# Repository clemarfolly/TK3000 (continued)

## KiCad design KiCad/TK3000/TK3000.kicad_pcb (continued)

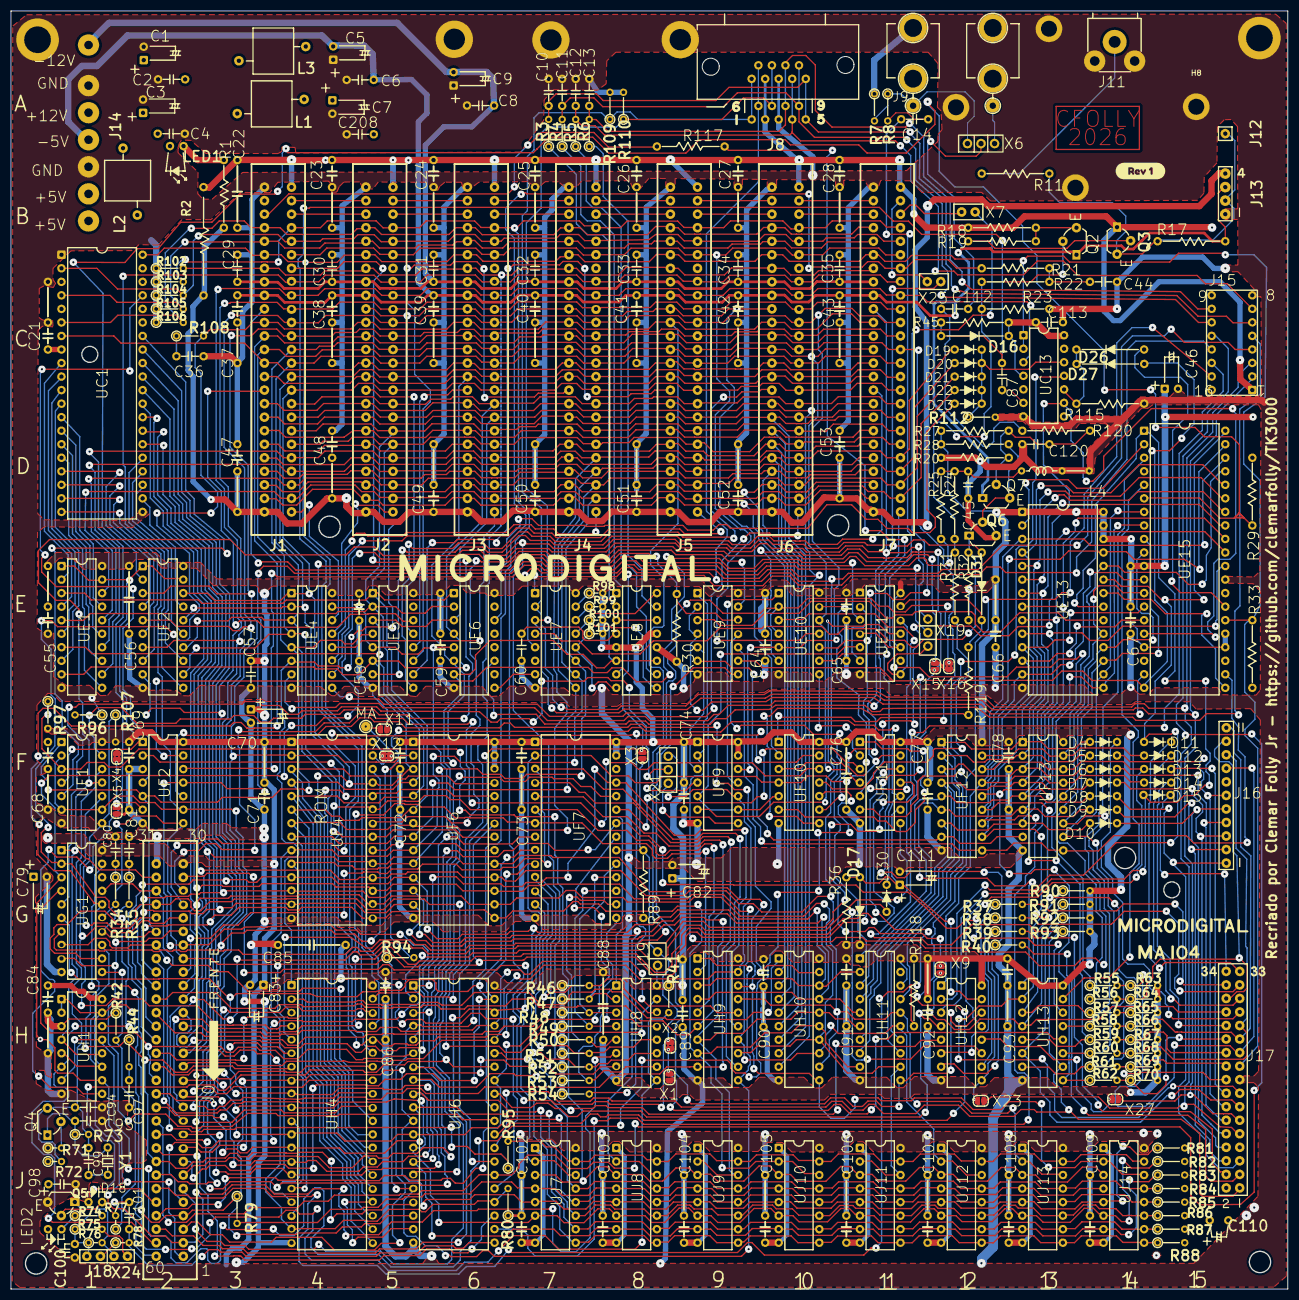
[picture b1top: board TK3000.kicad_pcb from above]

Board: 2 copper layers, 239.6 x 239.9 mm, 329 parts (0 on the bottom side), 320 nets.

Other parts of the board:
kibuzzard-6AD58770: G***; kibuzzard-6AD58770

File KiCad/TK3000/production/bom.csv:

Designator,Footprint,Quantity,Value,LCSC Part #
"C1, C111, C3, C5, C79, C82, C9",C_Elet_111,7,10uF,
"C10, C11, C12, C13",C_Disc_5.08,4,22nF,
C100,C_Disc_C100,1,100nF,
"C101, C112, C113, C2, C208, C29, C30, C31, C32, C33, C34, C35, C4, C57, C6, C8",C_Disc_5.08,16,100nF,
"C102, C103, C104, C105, C106, C107, C108, C109, C21, C23, C24, C25, C26, C27, C28, C37, C38, C39, C40, C41, C42, C43, C47, C48, C49, C50, C51, C52, C53, C55, C58, C59, C64, C66, C67, C68, C69, C71, C72, C73, C74, C77, C78, C84, C86, C89, C90, C91, C92, C93",C_Disc_5.08_12.7mm,50,100nF,
C110,C_Elet_C110,1,10uF,
"C120, C87",C_Disc_5.08,2,C,
C14,C_Disc_5.08,1,47nF,
"C22, C56, C76, C85, C88",C_Disc_12.7mm,5,100nF,
"C36, C80, C81, C97",C_Disc_5.08,4,220pF,
"C44, C94, C95",C_Disc_5.08,3,100pF,
C45,C_Disc_5.08,1,47pF,
"C46, C7, C70, C83",C_Elet_Tipo2,4,10uF,
C60,C_Disc_5.08,1,100n,
C65,C65_Disc_5.08_12.7mm,1,100nF,
C98,CP_Disc_5.08,1,10uF,
C99,C_Disc_5.08,1,33pF,
"D10, D11, D12, D13, D14, D15, D19, D20, D21, D22, D23, D30, D4, D5, D6, D7, D8, D9",D_5.08,18,1N914,
"D16, D17, D26, D27, D31",D_12.7,5,1N914,
D18,D_D18,1,1N914,
J0,SLOT-60_W5.08,1,~,
"J1, J2, J3, J4, J5, J6, J7",SLOT-50_W5.08,7,~,
J10,EarJack,1,EAR,
J11,"RCA_AV-8,4-5A",1,~,
J12,J12,1,Conn_01x01_Pin,
J13,J13,1,J13,
J14,J14,1,Power Connector,
J15,GAME_IO,1,~,
J16,J16,1,J16,
J17,J17,1,J17,
J18,J18,1,Alto-Falante,
J19,PinHeader_1x02_P2.54mm_Vertical,1,Conn_01x02_Pin,
J8,DB9,1,DE9_Socket,
J9,EarJack,1,EAR/MIC,
"L1, L2, L3",Ind,3,Ind,
L4,Ind_762,1,47uH,
LED1,led1,1,LED,
LED2,led2,1,LED,
"Q2, Q7",BC558,2,BC558,
"Q3, Q5, Q6",BC548,3,BC548,
Q4,BF494,1,BF494,
"R1, R17, R21",Resistor_P12.70mm_Horizontal,3,220R,
"R100, R101, R98, R99",Resistor_P2.54mm_Vertical,4,1k,
"R102, R46, R47, R48, R49, R50, R51, R52, R53, R54, R63, R64, R65, R66, R67, R68, R69, R70",Resistor_P5.08mm_Vertical,18,2k2,
"R103, R104, R105, R106, R107, R109, R110, R112, R41, R42, R55, R56, R57, R58, R59, R60, R61, R62, R90, R91, R92, R93, R94, R96, R97",Resistor_P5.08mm_Vertical,25,1k,
"R108, R34, R35, R44",Resistor_P5.08mm_Vertical,4,120R,
R11,Resistor_P12.70mm_Horizontal,1,100R,
"R115, R117, R118, R120, R18, R25, R29, R30, R31, R32, R89",Resistor_P12.70mm_Horizontal,11,1k,
R119,Resistor_P12.70mm_Horizontal,1,470R,
R19,Resistor_P12.70mm_Horizontal,1,47R,
R2,Res_20.32,1,100R/1W,
"R20, R33",Resistor_P12.70mm_Horizontal,2,4k7,
R22,Resistor_P12.70mm_Horizontal,1,5k6,
"R23, R24",Resistor_P12.70mm_Horizontal,2,6k8,
R27,Resistor_P12.70mm_Horizontal,1,220k,
R28,Resistor_P12.70mm_Horizontal,1,10k,
"R3, R4, R5, R6, R7, R74",Resistor_P5.08mm_Vertical,6,100R,
"R36, R45",Resistor_P12.70mm_Horizontal,2,2k2,
"R37, R38, R39, R40",Resistor_P5.08mm_Vertical,4,220,
R71,Resistor_P2.54mm_Vertical,1,47R,
R72,Resistor_P2.54mm_Vertical,1,470R,
R73,Resistor_P2.54mm_Vertical,1,22k,
R75,Resistor_P5.08mm_Vertical,1,33R,
R76,Resistor_P2.54mm_Vertical,1,75R,
R77,Resistor_P2.54mm_Vertical,1,51k,
R78,Resistor_P2.54mm_Vertical,1,3k3,
"R79, R95",Resistor_P5.08mm_Vertical,2,47R,
R8,Resistor_P5.08mm_Vertical,1,12k,
"R80, R81, R82, R83, R84, R85, R86, R87, R88",Resistor_P5.08mm_Vertical,9,22k,
UC1,DIP-40_W15.24mm,1,6502,
UC13,DIP-14_W7.62mm,1,74LS74,
"UE1, UE2",DIP-20_W7.62mm,2,74LS244,
UE10,UE10_DIP-14_W7.62mm,1,74LS32,
UE11,UE11_DIP-14_W7.62mm,1,74LS74,
UE13,DIP-28_W15.24mm,1,27C128,
UE15,DIP-40_W15.24mm,1,Z80A,
UE4,UE4_DIP-16_W7.62mm,1,74LS138,
"UE5, UE6",DIP-16_W7.62mm,2,74LS138,
UE7,DIP-16_W7.62mm,1,74LS251,
UE8,DIP-16_W7.62mm,1,NE558,
UE9,UE9_DIP-14_W7.62mm,1,74LS32,
UF1,DIP-14_W7.62mm,1,74LS125,
UF10,DIP-14_W7.62mm,1,74LS00,
UF11,DIP-14_W7.62mm,1,74LS08,
UF12,RAM_F12-13,1,2 x 2114,
UF2,DIP-14_W7.62mm,1,74S02,
UF4,ROM_F4-F6,1,27128,
UF7,UF7_DIP-28_W15.24mm,1,27C64,
UF9,DIP-14_W7.62mm,1,74LS86,
UG1,UG1_DIP-20_W7.62mm,1,PAL16R8,
UH1,DIP-16_W7.62mm,1,74S109,
UH10,DIP-20_W7.62mm,1,74LS245,
"UH11, UH9",DIP-20_W7.62mm,2,74LS374,
UH12,DIP-16_W7.62mm,1,74LS259,
UH13,DIP-16_W7.62mm,1,74LS365,
UH4,UH4_DIP-40_W15.24mm,1,MMU,
UH6,UH6_DIP-40_W15.24mm,1,IOU,
UH8,UH8_DIP-16_W7.62mm,1,74LS166,
UJ7,RAM_J7-J14,1,NMC3764,
"X25, X7",Jumper_2_Open,2,Jumper_2_Open,
Y1,XTAL,1,14.30244 MHz,
